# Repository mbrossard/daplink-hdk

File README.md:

# DAPLink HDK

## Introduction
This board is a hardware development kit created to make adding new HICs and features easier for the DAPLink firmware dev team.

# Upstream
You can find the upstream of this project here: [git.everydaydev.io](https://git.everydaydev.io/opensource/daplink-hdk)

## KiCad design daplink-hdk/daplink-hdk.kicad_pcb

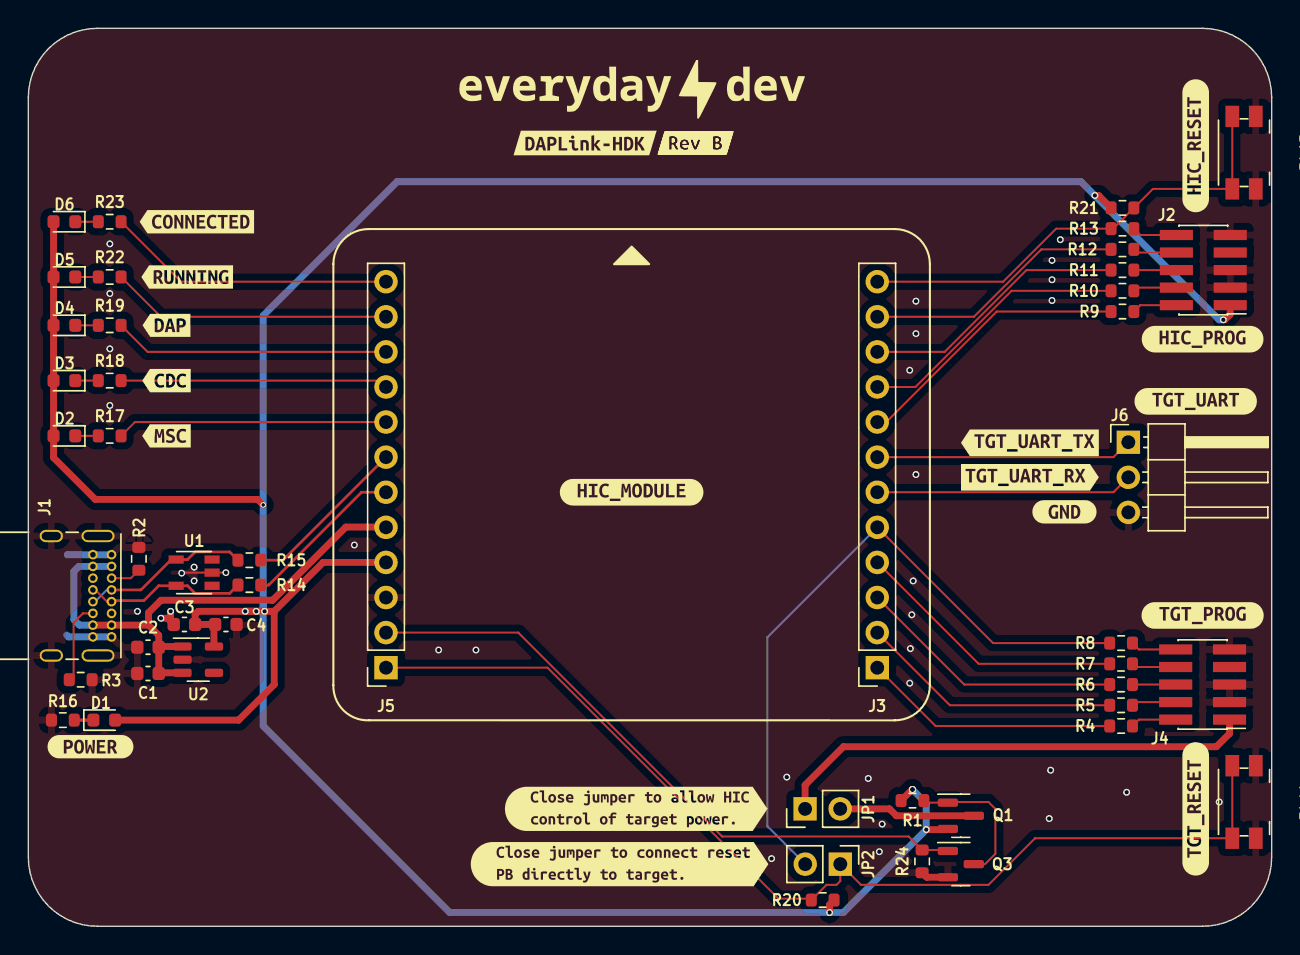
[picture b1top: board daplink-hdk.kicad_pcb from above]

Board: 2 copper layers, 90.0 x 65.0 mm, 68 parts (0 on the bottom side), 47 nets.

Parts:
C1, C4: 10u; C_0603_1608Metric
C2, C3: 0.1u; C_0603_1608Metric
D1, D2, D3, D4, D5, D6: RED; LED_0603_1608Metric
J1: USB_C_Receptacle_USB2.0; USB_C_Receptacle_GCT_USB4085
J2, J4: Conn_02x05_Odd_Even; PinHeader_2x05_P1.27mm_Vertical_SMD
J3, J5: Conn_01x12_Socket; PinSocket_1x12_P2.54mm_Vertical
J6: Conn_01x03; PinHeader_1x03_P2.54mm_Horizontal
JP1, JP2: Jumper_2_Open; PinHeader_1x02_P2.54mm_Vertical
Q1: DMP3099L; SOT-23
Q3: DMN3023L-7; SOT-23
R1, R20, R21, R24: 10k; R_0603_1608Metric
R2, R3: 5.1k; R_0603_1608Metric
R4, R5, R6, R7, R8, R9, R10, R11, R12, R13: 100R; R_0603_1608Metric
R14, R15: 22R; R_0603_1608Metric
R16, R17, R18, R19, R22, R23: 1k; R_0603_1608Metric
SW1, SW2: SW_Push; Panasonic_EVQPUJ_EVQPUA
U1: ESDS302DBVR; SOIC-6
U2: AP2127K-3.3; SOT-23-5
kibuzzard-65CA7DAF: G***; kibuzzard-65CA7DAF
kibuzzard-65CA74FC: G***; kibuzzard-65CA74FC
kibuzzard-6546A6D3: G***; kibuzzard-6546A6D3
kibuzzard-6546A6DC: G***; kibuzzard-6546A6DC
kibuzzard-6546A6ED: G***; kibuzzard-6546A6ED
kibuzzard-6546A6F2: G***; kibuzzard-6546A6F2
kibuzzard-6546A65D: G***; kibuzzard-6546A65D
kibuzzard-6546A67F: G***; kibuzzard-6546A67F
kibuzzard-6546A68D: G***; kibuzzard-6546A68D
kibuzzard-6546A74E: G***; kibuzzard-6546A74E
kibuzzard-6546A77C: G***; kibuzzard-6546A77C
kibuzzard-6546A89A: G***; kibuzzard-6546A89A
kibuzzard-6546A714: G***; kibuzzard-6546A714
kibuzzard-6546A755: G***; kibuzzard-6546A755
kibuzzard-6546A761: G***; kibuzzard-6546A761
kibuzzard-6546A773: G***; kibuzzard-6546A773
kibuzzard-6546A850: G***; kibuzzard-6546A850
kibuzzard-6546A856: G***; kibuzzard-6546A856
kibuzzard-6546AB1F: G***; kibuzzard-6546AB1F
kibuzzard-6548DE83: G***; kibuzzard-6548DE83

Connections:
+3V3: C3.2, C4.2, D1.2 (A), D2.2 (A), D3.2 (A), D4.2 (A), D5.2 (A), D6.2 (A), J2.1, J5.4, Q1.2 (S), R1.2, R20.2, R21.2, U2.5 (VOUT)
/HIC_TCK_SWCLK: J3.9, R10.1
/HIC_TDI: J3.11, R12.1
/HIC_TDO_SWO: J3.10, R11.1
/HIC_TMS_SWDIO: J3.8, R9.1
/HIC_USB_N: J5.6, R14.2
/HIC_USB_P: J5.7, R15.2
/HIC_nRESET: J3.12, R13.1, R21.1, SW2.2
/LED_CDC: J5.9, R18.2
/LED_CONNECTED: J5.12, R23.2
/LED_HID: J5.10, R19.2
/LED_MSC: J5.8, R17.2
/LED_RUNNING: J5.11, R22.2
/TGT_PWR_EN: J5.2, Q3.1 (G), R24.2
/TGT_TCK_SWCLK: J3.2, R5.1
/TGT_TDI: J3.4, R7.1
/TGT_TDO_SWO: J3.3, R6.1
/TGT_TMS_SWDIO: J3.1, R4.1
/TGT_UART_RX: J3.6, J6.2
/TGT_UART_TX: J3.7, J6.1
/TGT_nRESET_FWRD: J5.1, JP2.1 (A), R20.1, SW1.2
/TGT_nRESET_OUT: J3.5, JP2.2 (B), R8.1
/USB_N: J1.A7 (D-), J1.B7 (D-), R14.1, U1.5 (IO2)
/USB_P: J1.A6 (D+), J1.B6 (D+), R15.1, U1.4 (IO1)
GND: C1.1, C2.1, C3.1, C4.1, J1.A1 (GND), J1.A12 (GND), J1.B1 (GND), J1.B12 (GND), J1.S1 (SHIELD), J2.3, J2.5, J2.9, J4.3, J4.5, J4.9, J5.3, J6.3, Q3.2 (S), R2.2, R3.2, R16.2, R24.1, SW1.1, SW2.1, U1.2 (GND), U2.2 (GND)
unnamed: D1.1 (K), R16.1
unnamed: D2.1 (K), R17.1
unnamed: D3.1 (K), R18.1
unnamed: D4.1 (K), R19.1
unnamed: D5.1 (K), R22.1
unnamed: D6.1 (K), R23.1
unnamed: J1.A5 (CC1), R2.1
unnamed: J1.B5 (CC2), R3.1
unnamed: J2.2, R9.2
unnamed: J2.4, R10.2
unnamed: J2.6, R11.2
unnamed: J2.8, R12.2
unnamed: J2.10, R13.2
unnamed: J4.1, JP1.1 (A)
unnamed: J4.2, R4.2
unnamed: J4.4, R5.2
unnamed: J4.6, R6.2
unnamed: J4.8, R7.2
unnamed: J4.10, R8.2
unnamed: JP1.2 (B), Q1.3 (D)
unnamed: Q1.1 (G), Q3.3 (D), R1.1
VBUS: C1.2, C2.2, J1.A4 (VBUS), J1.A9 (VBUS), J1.B4 (VBUS), J1.B9 (VBUS), J5.5, U2.1 (VIN), U2.3 (EN)

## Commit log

2023-11-30 Ready for release
2023-11-30 Remove lck files
2023-11-30 Update readme img name
2023-12-01 Update project name to daplink-hdk
2023-12-01 Update revision to Rev A
2024-02-12 Fix missing power LED trace, increment rev, and add Gitlab CI
2024-02-28 Limit layers exported

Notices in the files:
README.md:
CC by SA
